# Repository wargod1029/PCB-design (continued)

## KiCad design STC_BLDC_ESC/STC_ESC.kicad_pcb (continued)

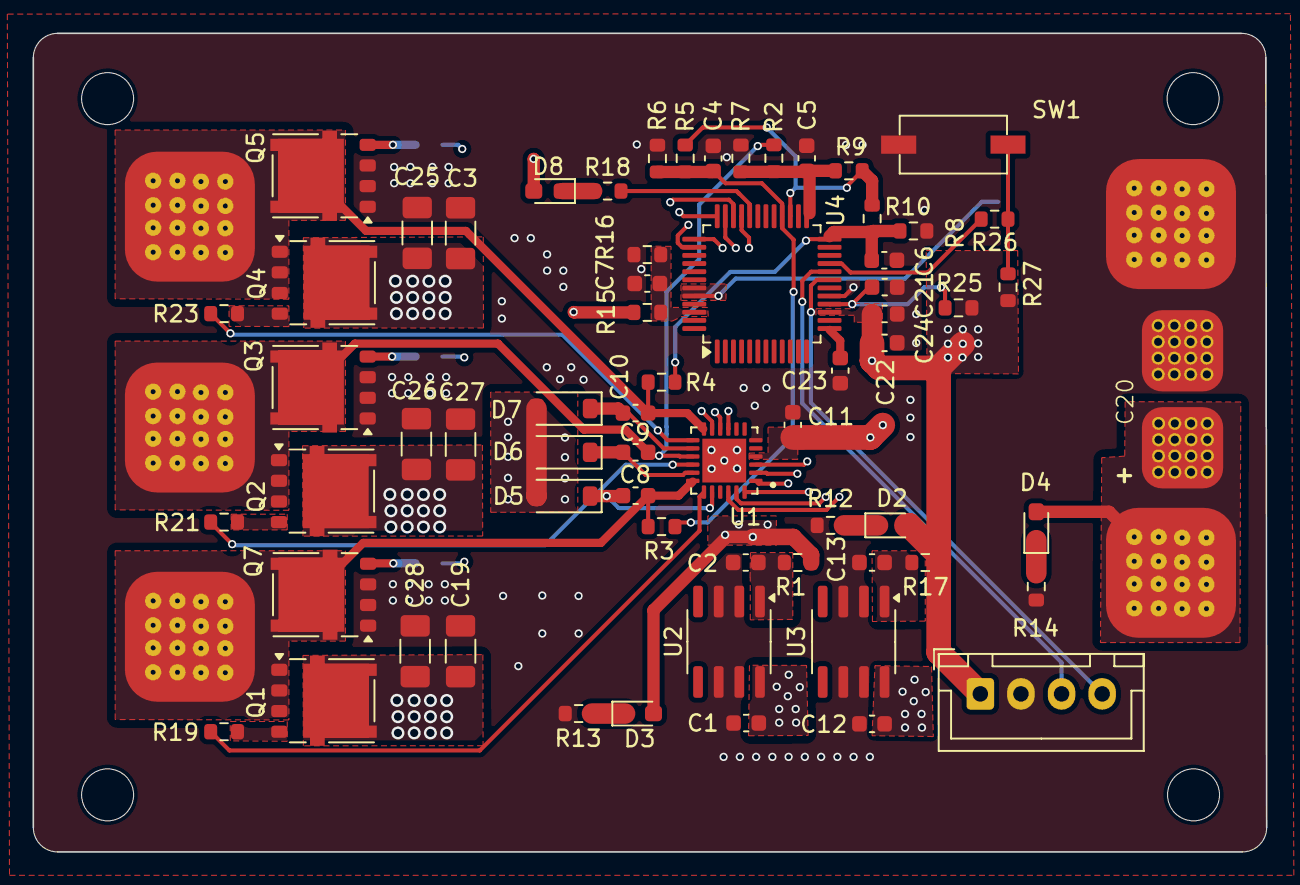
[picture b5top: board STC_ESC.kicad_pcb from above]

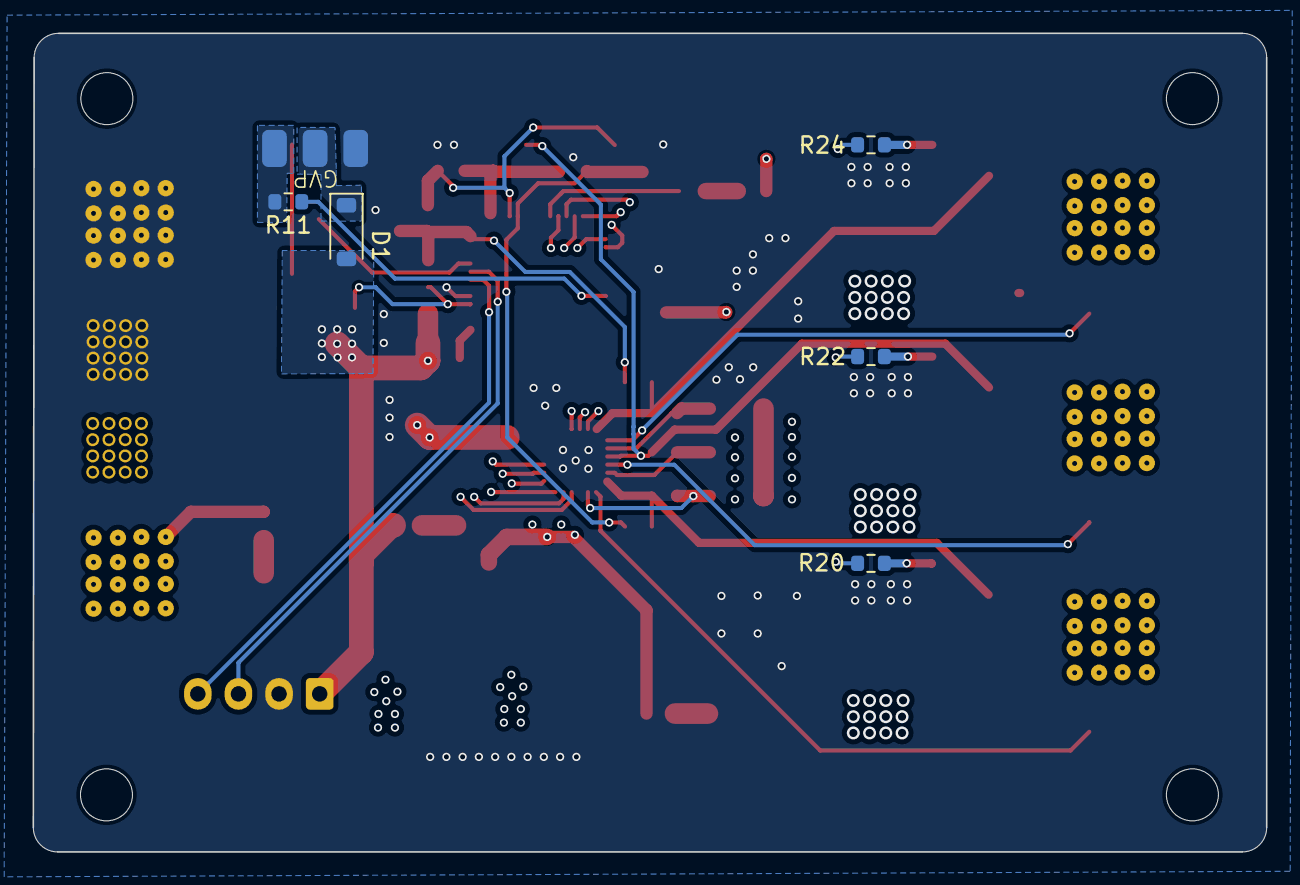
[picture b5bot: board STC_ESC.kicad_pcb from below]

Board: 4 copper layers, 75.9 x 50.4 mm, 80 parts (6 on the bottom side), 49 nets.

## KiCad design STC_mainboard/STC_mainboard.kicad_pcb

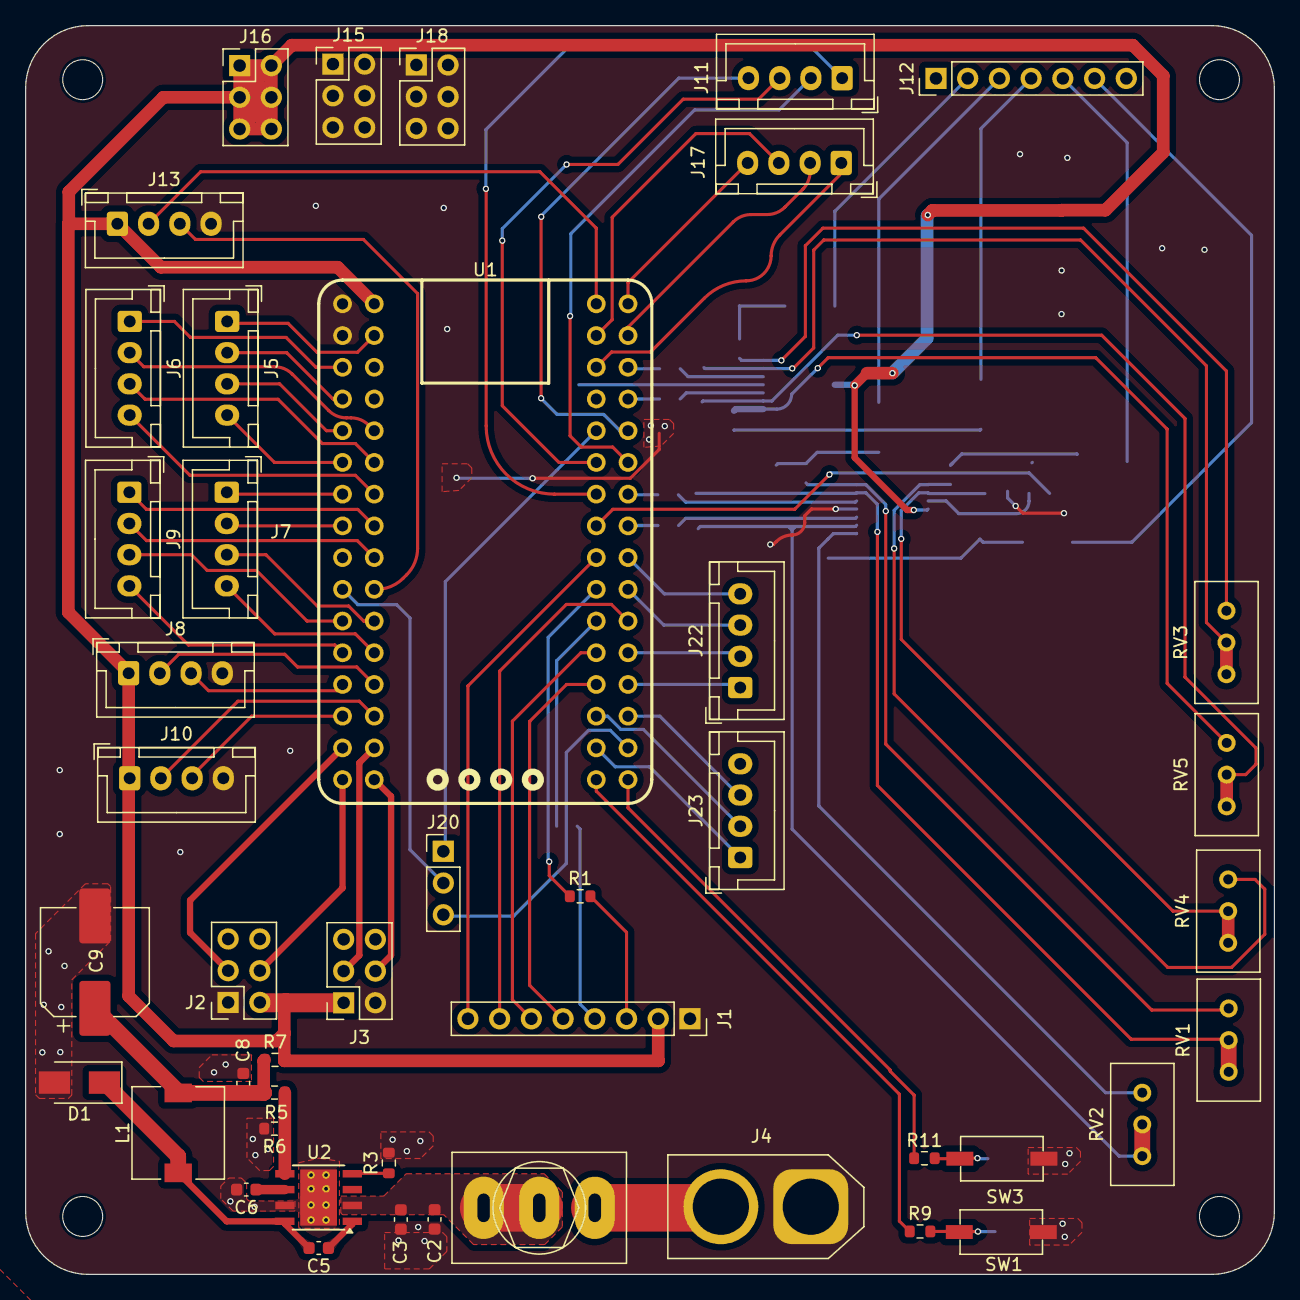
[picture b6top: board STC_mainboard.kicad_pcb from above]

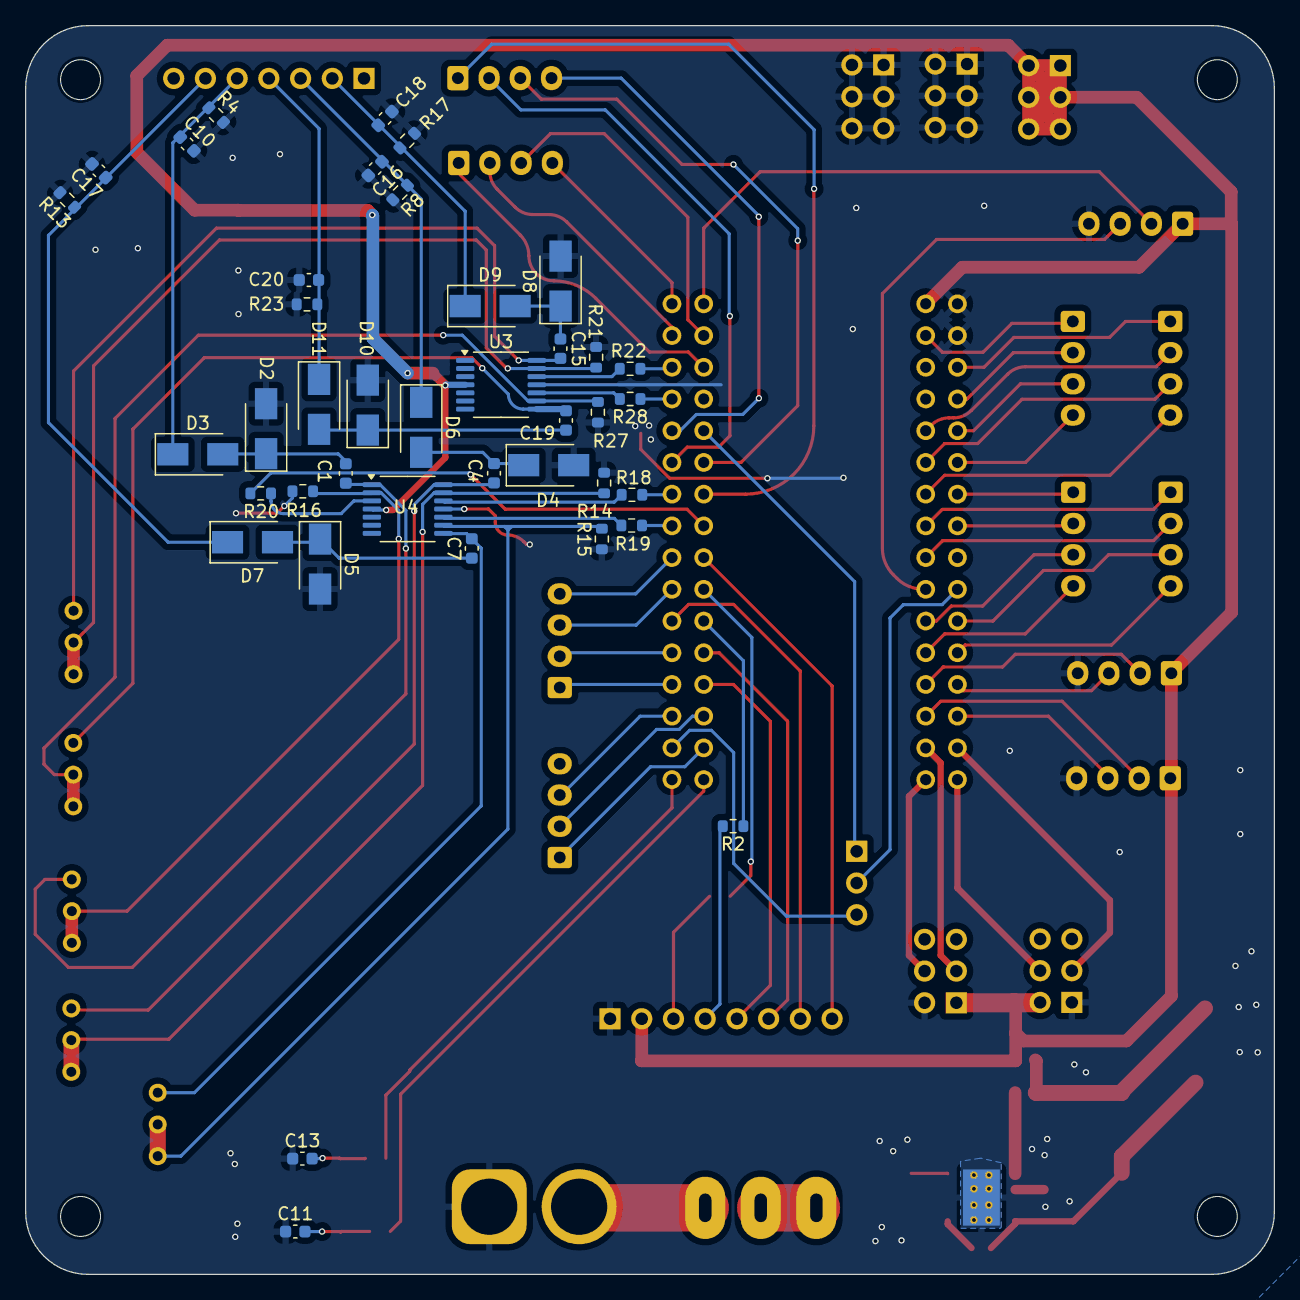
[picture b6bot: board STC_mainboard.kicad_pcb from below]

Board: 2 copper layers, 100.0 x 100.0 mm, 89 parts (40 on the bottom side), 96 nets.

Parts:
C1, C4, C5, C7, C10, C11, C13, C15, C16, C17, C18, C19, C20: 100nF; C_0603_1608Metric
C2, C3: 2.2uF; C_0603_1608Metric
C6: 39F; C_0603_1608Metric
C8: 39pF; C_0603_1608Metric
C9: 1000uF; CP_Elec_8x10.5
D1, D2, D3, D4, D5, D6, D7, D8, D9, D10, D11: SS54; D_SMA
H1, H2, H3, H4: MountingHole; MountingHole_3.2mm_M3
J1: Conn_01x08; PinSocket_1x08_P2.54mm_Vertical
J2, J3: Conn_02x03_Odd_Even; PinSocket_2x03_P2.54mm_Vertical
J4: Conn_01x02; AMASS_XT60-F_1x02_P7.20mm_Vertical
J5, J6, J7, J8, J9, J10, J11, J13, J17, J22, J23: Conn_01x04; JST_XH_B4B-XH-A_1x04_P2.50mm_Vertical
J12: Conn_01x07; PinHeader_1x07_P2.54mm_Vertical
J15, J16, J18: Conn_02x03_Odd_Even; PinHeader_2x03_P2.54mm_Vertical
J20: Conn_01x03; PinHeader_1x03_P2.54mm_Vertical
L1: 22uH; L_7.3x7.3_H3.5
PSW1: SW_SPDT; SW_Toggle_Blue_wSlots
R1, R2, R9, R11, R14, R15, R16, R21, R27: 100R; R_0603_1608Metric
R3: 162k; R_0603_1608Metric
R4, R8, R13, R17, R23: 51k; R_0603_1608Metric
R5: 53.6k; R_0603_1608Metric
R6: 10.2k; R_0603_1608Metric
R7: 0R; R_0603_1608Metric
R18, R19, R20, R22, R28: 5.1k; R_0603_1608Metric
RV1, RV2, RV3, RV4, RV5: 100k; Potentiometer_Bourns_3296W_Vertical
SW1, SW3: SW_Push
U1: STC16H40K128_CoreBoard; STC16F40K128_CoreBoard
U2: TPS54360DDA; TI_SO-PowerPAD-8_ThermalVias
U3, U4: OPA4197xPW; TSSOP-14_4.4x5mm_P0.65mm

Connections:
+5V: J1.2, J2.2, J3.1, J8.1, J10.1, J13.1, J16.1, J16.2, J16.3, J16.4, J16.5, J16.6, R7.2, U1.2 (VCC), U3.4 (V+), U4.4 (V+)
+12V: C2.1, C3.1, PSW1.1 (A), PSW1.2 (B), U2.2 (VIN)
/FB: R5.2, R6.1, U2.5 (FB)
/L1: C18.1, D9.1 (K), J12.2, R17.1
/L2: C16.1, D6.1 (K), J12.3, R8.1
/L3: C20.1, D11.1 (K), J12.4, R23.1
/L4: C10.1, D3.1 (K), J12.5, R4.1
/L5: C17.1, D7.1 (K), J12.6, R13.1
/P0.0: R19.1, U1.50 (0.0)
/P0.1: R20.1, U1.49 (0.1)
/P0.2: R18.1, U1.52 (0.2)
/P0.3: R28.1, U1.58 (0.3)
/P0.5: R22.1, U1.60 (0.5)
/P0.6: J17.1, U1.59 (0.6)
/P0.7: J17.2, U1.62 (0.7)
/P1.0: J17.3, U1.61 (1.0)
/P1.1: J6.1, U1.5 (1.1)
/P1.3: J5.2, U1.7 (1.3)
/P1.4: J6.4, U1.14 (1.4)
/P1.5: J9.1, U1.16 (1.5)
/P1.6: J7.2, U1.15 (1.6)
/P1.7: J9.2, U1.18 (1.7)
/P2.0: J1.5, U1.39 (2.0)
/P2.1: J1.6, U1.41 (2.1)
/P2.2: J1.7, U1.44 (2.2)
/P2.3: R2.1, U1.43 (2.3)
/P2.4: J22.3, U1.46 (2.4)
/P2.5: R1.1, U1.45 (2.5)
/P2.6: J22.4, U1.48 (2.6)
/P2.7: J1.8, U1.47 (2.7)
/P3.0: J8.2, U1.26 (3.0)
/P3.1: J8.3, U1.25 (3.1)
/P3.2: J10.2, U1.28 (3.2)
/P3.3: J10.3, U1.27 (3.3)
/P3.4: J3.3, U1.30 (3.4)
/P3.5: J2.3, U1.29 (3.5)
/P3.6: R11.1, U1.34 (3.6)
/P3.7: R9.1, U1.33 (3.7)
/P4.0: J20.2, U1.19 (4.0)
/P4.1: J20.3, U1.36 (4.1)
/P4.2: J22.2, U1.42 (4.2)
/P4.3: J20.1, U1.55 (4.3)
/P4.4: J7.1, U1.13 (4.4)
/P4.5: J17.4, U1.64 (4.5)
/P4.6: J13.2, U1.63 (4.6)
/P4.7: J13.3, U1.20 (4.7)
/P5.0: J3.4, U1.32 (5.0)
/P5.1: J2.4, U1.31 (5.1)
/P5.2: J5.1, U1.4 (5.2)
/P6.0: J6.2, U1.10 (6.0)
/P6.1: J5.3, U1.9 (6.1)
/P6.2: J6.3, U1.12 (6.2)
/P6.3: J5.4, U1.11 (6.3)
/P6.4: J7.3, U1.22 (6.4)
/P6.5: J9.3, U1.21 (6.5)
/P6.6: J7.4, U1.24 (6.6)
/P6.7: J9.4, U1.23 (6.7)
/P7.0: J23.1, U1.35 (7.0)
/P7.1: J23.3, U1.38 (7.1)
/P7.2: J23.2, U1.37 (7.2)
/P7.3: J22.1, U1.40 (7.3)
/P7.4: J11.1, U1.51 (7.4)
/P7.5: J11.2, U1.54 (7.5)
/P7.6: J11.3, U1.53 (7.6)
/P7.7: J11.4, U1.56 (7.7)
GND: C2.2, C3.2, C6.2, C8.2, C9.2, C10.2, C11.1, C13.1, C16.2, C17.2, C18.2, C20.2, D1.2 (A), D2.2 (A), D4.2 (A), D5.2 (A), D8.2 (A), D10.2 (A), J1.1, J2.1, J3.2, J4.1, J8.4, J10.4, J13.4, J15.1, J15.2, J15.3, J15.4, J15.5, J15.6, J18.1, J18.2, J18.3, J18.4, J18.5, J18.6, R3.2, R4.2, R6.2, R8.2, R13.2, R14.1, R15.1, R16.1, R17.2, R21.1, R23.2, R27.1, SW1.1, SW3.1, U1.1 (GND), U1.3 (GND), U2.7 (GND), U2.9 (GNDPAD), U3.11 (V-), U4.11 (V-)
unnamed: C1.2, RV4.1, U4.1
unnamed: C4.2, RV1.1, U4.14
unnamed: C7.2, RV2.1, U4.8
unnamed: C8.1, C9.1, L1.2, R5.1, R7.1
unnamed: C11.2, R9.2, SW1.2
unnamed: C13.2, R11.2, SW3.2
unnamed: C15.2, RV3.1, U3.14
unnamed: C19.2, RV5.1, U3.8
unnamed: C5.2, D1.1 (K), L1.1, U2.8 (SW)
unnamed: C1.1, D2.1 (K), D3.2 (A)
unnamed: C4.1, D4.1 (K), D6.2 (A)
unnamed: C7.1, D5.1 (K), D7.2 (A)
unnamed: C15.1, D8.1 (K), D9.2 (A)
unnamed: C19.1, D10.1 (K), D11.2 (A)
unnamed: J1.3, R1.2
unnamed: J1.4, R2.2
unnamed: J4.2, PSW1.3 (C)
unnamed: C5.1, U2.1 (BOOT)
unnamed: C6.1, U2.6 (COMP)
unnamed: R3.1, U2.4 (RT/CLK)
unnamed: R28.2, U3.10 (+)
unnamed: R27.2, RV5.2, RV5.3, U3.9 (-)
unnamed: R22.2, U3.12 (+)
unnamed: R21.2, RV3.2, RV3.3, U3.13 (-)
unnamed: R20.2, U4.3 (+)
unnamed: R16.2, RV4.2, RV4.3, U4.2 (-)
unnamed: R19.2, U4.10 (+)
unnamed: R15.2, RV2.2, RV2.3, U4.9 (-)
unnamed: R18.2, U4.12 (+)
unnamed: R14.2, RV1.2, RV1.3, U4.13 (-)
